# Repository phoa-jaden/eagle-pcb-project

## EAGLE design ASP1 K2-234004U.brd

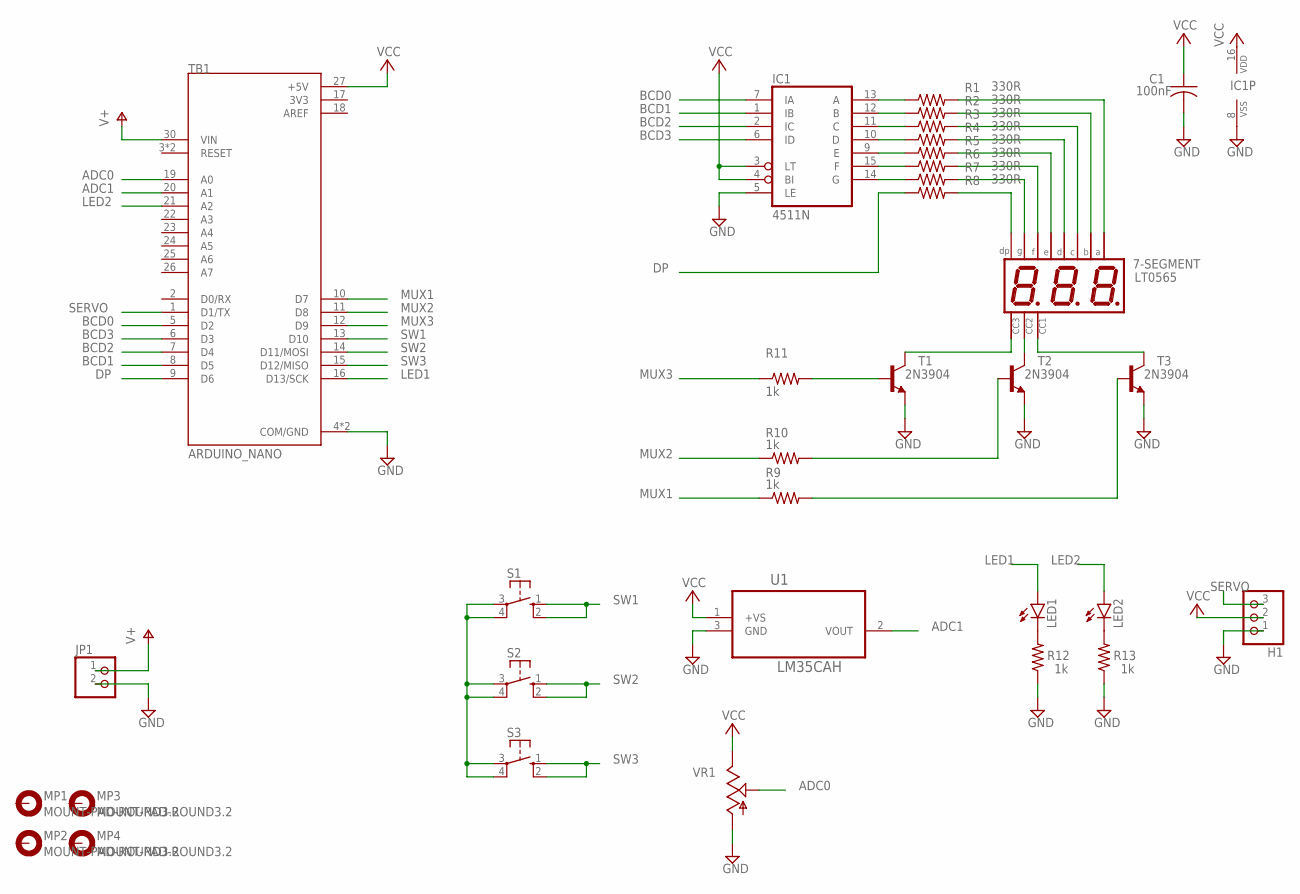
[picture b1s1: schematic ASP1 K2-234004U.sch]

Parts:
7-SEGMENT: LT0565; BX56/BX55
C1: 100nF; C050-024X044
H1: PINHD-1X3; 1X03
IC1: 4511N; DIL16
JP1: PINHD-1X2; 1X02
LED1, LED2: LED3MM
MP1, MP2, MP3, MP4: MOUNT-PAD-ROUND3.2; 3,2-PAD
R1, R2, R3, R4, R5, R6, R7, R8: 330R; 0207/10
R9, R10, R11, R12, R13: 1k; 0207/10
S1, S2, S3: 10-XX; B3F-10XX
T1, T2, T3: 2N3904; TO92
TB1: ARDUINO_NANO; SHIELD_ARDUINO_NANO
U1: LM35CAH; TO127P543X266-3P
VR1: POTENTIOMETER_PT10; PT-10

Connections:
3V3: TB1.17 (3V3)
ADC0: TB1.19 (A0), VR1.3 (S)
ADC1: TB1.20 (A1), U1.2 (VOUT)
AREF: TB1.18 (AREF)
BCD0: IC1.7 (IA), TB1.5 (D2)
BCD1: IC1.1 (IB), TB1.8 (D5)
BCD2: IC1.2 (IC), TB1.7 (D4)
BCD3: IC1.6 (ID), TB1.6 (D3)
DP: R8.1, TB1.9 (D6)
GND: C1.2, H1.1, IC1.5 (LE), IC1.8 (VSS), JP1.2, R12.1, R13.1, T1.3 (E), T2.3 (E), T3.3 (E), TB1.4 (COM/GND), TB1.29 (COM/GND), U1.3 (GND), VR1.1 (A)
LED1: LED1.A, TB1.16 (D13/SCK)
LED2: LED2.A, TB1.21 (A2)
MUX1: R9.1, TB1.10 (D7)
MUX2: R10.1, TB1.11 (D8)
MUX3: R11.1, TB1.12 (D9)
unnamed: S1.3, S1.4 (P1), S2.3, S2.4 (P1), S3.3, S3.4 (P1)
unnamed: LED2.K (C), R13.2
unnamed: LED1.K (C), R12.2
unnamed: IC1.13 (A), R1.1
unnamed: IC1.12 (B), R2.1
unnamed: IC1.11 (C), R3.1
unnamed: IC1.10 (D), R4.1
unnamed: IC1.9 (E), R5.1
unnamed: IC1.15 (F), R6.1
unnamed: IC1.14 (G), R7.1
unnamed: 7-SEGMENT.3 (DP), R8.2
unnamed: 7-SEGMENT.5 (G), R7.2
unnamed: 7-SEGMENT.10 (F), R6.2
unnamed: 7-SEGMENT.1 (E), R5.2
unnamed: 7-SEGMENT.2 (D), R4.2
unnamed: 7-SEGMENT.4 (C), R3.2
unnamed: 7-SEGMENT.11 (A), R1.2
unnamed: 7-SEGMENT.7 (B), R2.2
unnamed: 7-SEGMENT.9 (CA), T2.1 (C)
unnamed: 7-SEGMENT.12 (CA), T3.1 (C)
unnamed: 7-SEGMENT.8 (CA), T1.1 (C)
unnamed: R10.2, T2.2 (B)
unnamed: R9.2, T3.2 (B)
unnamed: R11.2, T1.2 (B)
SERVO: H1.3, TB1.1 (D1/TX)
SW1: S1.1 (S), S1.2 (S1), TB1.13 (D10)
SW2: S2.1 (S), S2.2 (S1), TB1.14 (D11/MOSI)
SW3: S3.1 (S), S3.2 (S1), TB1.15 (D12/MISO)
V+: JP1.1, TB1.30 (VIN)
VCC: C1.1, H1.2, IC1.3 (LT), IC1.4 (BI), IC1.16 (VDD), TB1.27 (+5V), U1.1 (+VS), VR1.2 (E)

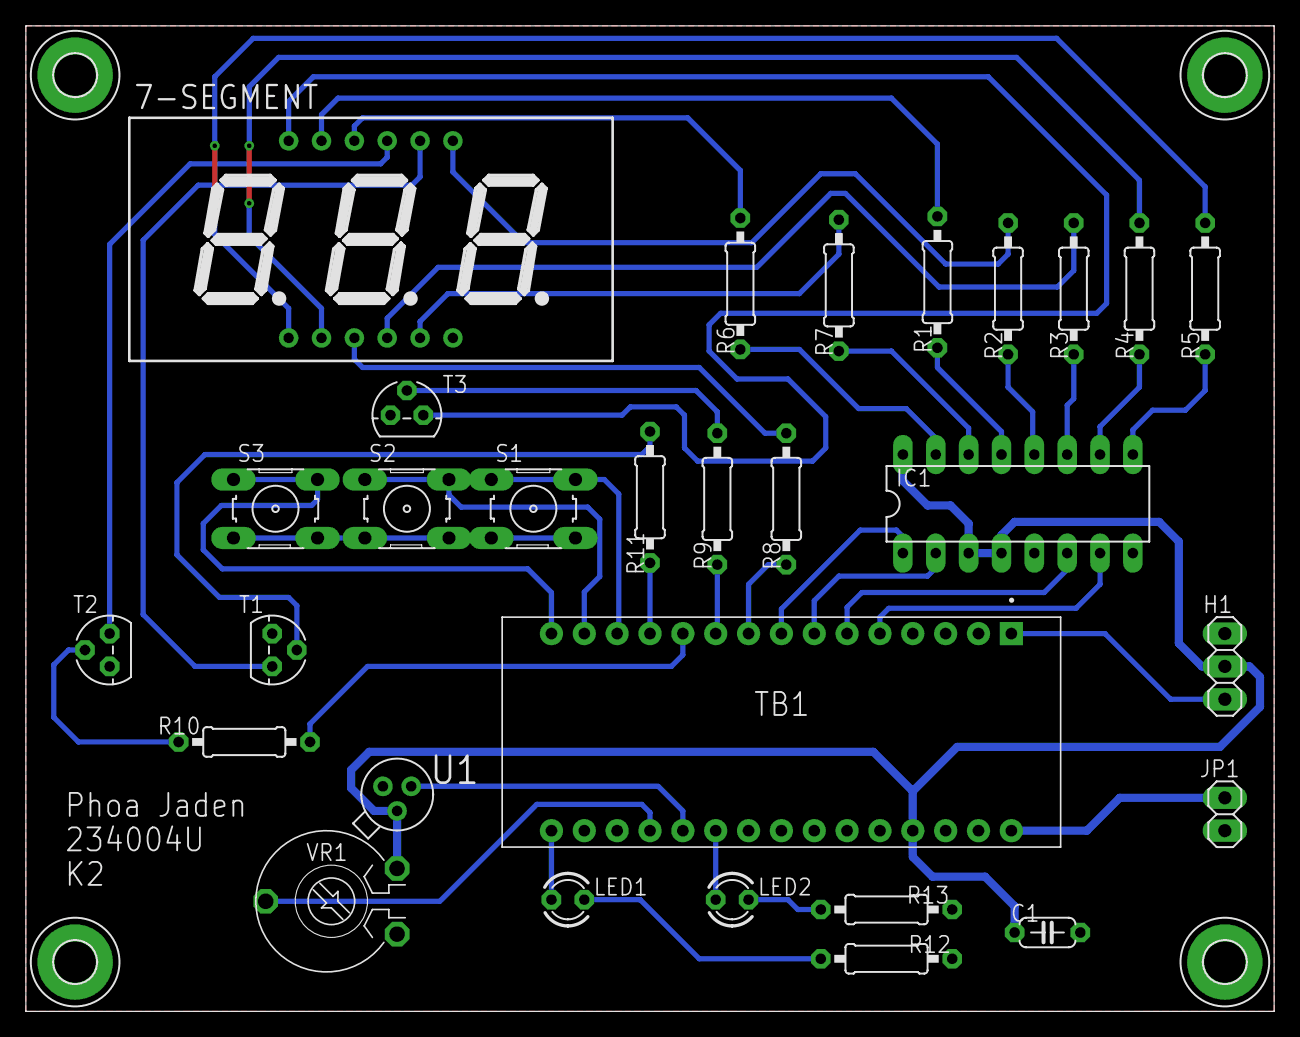
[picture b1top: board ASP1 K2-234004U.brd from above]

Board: 2 copper layers, 96.5 x 76.2 mm, 33 parts (0 on the bottom side), 43 nets.
